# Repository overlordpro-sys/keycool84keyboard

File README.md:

# How I Made My Mechanical Keyboard ([Youtube Video](https://www.youtube.com/watch?v=BKlyYG0T2mQ))

About a year ago, I was looking into getting a new mechanical keyboard with linear switches. I had grown tired of the name brand keyboards like Corsair and Logitech who did not lubricate their switches. This made each keypress loud and unsatisfying. After doing some research, I decided to build my own instead of buying it. Most people who build custom keyboards buy a predesigned PCB. However, I wanted to design the PCB myself because I thought it would be fun. In the end, that proved true and I learned a lot about the inner workings of mechanical keyboards and PCB design. 

## Design

The switch layout I chose was the Keycool84 layout, featuring both arrow keys and a function row while still being relatively compact. After spending a day or two thinking about how to piece each component together, the design I went with featured a metal plate, 4 M4x10 bolts, two 3D printed supports for the bolts in the middle layer, and the PCB on the bottom. The bolts would also serve as a stand and create a slight incline. By using supports in between, I could avoid having to 3D print and piece together a large case that mechanical keyboards usually have. The Arduino would be placed to the side under one of the bolts. 

To get an accurate outline for the keyboard, I used the Keycool84 preset layout on keyboard-layout-editor.com.
In addition, I selected all of the keys and set each switch to use Cherry MX Kailh switch cutouts for my switch of choice, Kailh speed silvers, so I could use it to help with the plate cutout later on.

I transfered the raw data from the layout editor to a [plate and case builder website](http://builder.swillkb.com/) to generate a DXF file that I could actually use in KiCAD.

## Wiring

The most important part of this keyboard is naturally its wiring. Technically, each switch could be wired to two pins to detect switch input. This obviously is extremely inefficient and would use a lot of pins. The solution to this problem is wiring the switches in a gridlike manner. One issue with this, is that if multiple keys are pressed, some keypresses can be registered incorrectly due to current traveling backwards. This is solved by placing a diode with each switch to prevent this backwards flow and makes each keypress distinguishable from other keys by the Arduino. Each switch is wired approximately like so:

The last thing to consider was the location for each switch in the 6x14 grid. To get an idea of where each switch on the grid should be placed, I sketched it out in an app. 

## The PCB

The next step was designing the PCB for this keyboard. For simplicity and to ensure I had enough pins, I decided to use an Arduino Pro Micro for the controller. 
For the symbols and footprints for the switches and Arduino, I used two KiCad libraries:
https://github.com/ai03-2725/MX_Alps_Hybrid 
https://github.com/Biacco42/ProMicroKiCad 

For the necessary diodes, I downloaded the ECAD Model for the [1N4148W-7-F diode](https://www.mouser.co.uk/ProductDetail/Diodes-Incorporated/1N4148W-7-F?qs=LHX0FizJzg7Ae9ZM8LTAWw%3D%3D) at Mouser Electronics  and converted it into a KiCad library using the Mouser LibraryLoader. 

After including the libraries in my KiCad project file, I first wired the switches in a grid format in the schematics file. Then I assigned each row and column to a pin on the Arduino's symbol.

After I was finished with the schematic, I used KiCad's Pcbnew to design the PCB. Using the DXF file I generated before, I imported the file and moved each associated switch and diode footprint to each cutout on the DXF. I placed the Arduino's footprint to the left and drew a border around the entire PCB. To be able to secure my keyboard plate to the PCB, I also added four holes with a diameter slightly larger than the bolt diameter on each corner where I could use a nut and bolt. 

After placing all of the footprints, I routed the PCB using Freerouter. Overall, the board was simple and using an autorouter wouldn't cause any issues.

After adding some silkscreeneening out of curiosity, this was the finished result:

Using the built in 3D PCB viewer, took a look at the 3D model of what the PCB would look like. It was really neat seeing something I had designed myself.

After generating the neccessary Gerber files, I placed my order with JLCPCB and chose a white PCB. Here's what the PCBs looked like when they came:

## The Plate
The easiest way to maintain the same size and location for the screw holes was to make a copy of the old PCB file. After removing the switches, diodes, and Arduino footprints on the duplicate project, I ended up with a plain outline with screw holes. 

After exporting that to a DXF and removing any duplicate geometry in LibreCAD, it was ready to be cut.

After doing some research, I chose SendCutSend to cut my plate. In order for the switches to slot into the plate, the plate had to be a certain width, so the 0.060 inch (about 1.5mm) thick stainless steel material SendCutSend supplied was great. 

Unfortunately, I didn't take a very good picture before I soldered everything together, so this is the only picture I have of the plate by itself. 

## 3D Printing the middle

At first, I wanted to make a case that would encompass the entirety of the keyboard. However, the 3D printer I had at home would not be large enough to print it in one piece. Printing it in multiple pieces would require me to glue the pieces together and would make it less durable. I also didn't want to bother sending an order to a third party printing service and increasing my total build cost. At the very least, I wanted to make something that would fill some of the ugly gap between the plate and PCB. Filling in the gaps in the front and back of the keyboard would make it too large to print on my printer, so I could only make something for the right and left. In the end, I decided to make two rectangles with the cutouts for the bolts. 

In order to move it from KiCad to my modeling software of choice, Fusion 360, I plotted it into a DXF file and imported it with a 3.5mm thickness (approximate amount of space between the PCB and plate) using [DXF Import Utility.](https://apps.autodesk.com/FUSION/en/Detail/Index?id=3146198746757677787&appLang=en&os=Win64) 

After that, I exported each part into Cura with Fusion's built in exporter, merged the models into one project, and exported the G-code file for my 3D printer. 

## Software
To communicate the keystrokes, I used the Arduino libraries [Keypad](https://playground.arduino.cc/Code/Keypad/) and [Keyboard](https://www.arduino.cc/reference/en/language/functions/usb/keyboard/). The best thing about the Keypad library is that it supports N-key rollover to intepret multiple keypresses at the same time. For my keyboard, I edited Keypad's provided example. I added which keys I needed, edited the pins to use, and had it use Keyboard to send keystrokes instead of just printing them to console. 

```javascript
#include <Keypad.h>
#include <Keyboard.h>

const byte ROWS = 6;
const byte COLS = 14; 
char keys[ROWS][COLS] = {
  {KEY_ESC,KEY_F1,KEY_F2,KEY_F3,KEY_F4,KEY_F5,KEY_F6,KEY_F7,KEY_F8,KEY_F9,KEY_F10,KEY_F11,206,KEY_HOME},
  {'`','1','2','3','4','5','6','7','9','0','-',KEY_F12,KEY_INSERT,KEY_PAGE_UP},
  {KEY_TAB,'q','w','e','r','t','y','8','o','p','[','=',KEY_BACKSPACE,KEY_PAGE_DOWN},
  {KEY_CAPS_LOCK,'a','s','d','f','g','u','i','l',';',39,']',92,KEY_DELETE},
  {KEY_LEFT_SHIFT,'z','x','c','v','h','j','k','.','/',KEY_RIGHT_SHIFT,KEY_RETURN,KEY_UP_ARROW,' '},
  {KEY_LEFT_CTRL,KEY_LEFT_GUI,KEY_LEFT_ALT,32,'b','n','m',',',KEY_RIGHT_ALT,KEY_RIGHT_GUI,KEY_RIGHT_CTRL,KEY_LEFT_ARROW,KEY_DOWN_ARROW,KEY_RIGHT_ARROW}
};

byte rowPins[ROWS] = {18,19,20,21,22,23}; 
byte colPins[COLS] = {13,12,11,10,9,8,7,6,5,4,3,2,0,1}; 
Keypad kpd = Keypad( makeKeymap(keys), rowPins, colPins, ROWS, COLS );

void setup() {
    Keyboard.begin();
}

void loop() {
    if (kpd.getKeys())
    {
        for (int i=0; i<LIST_MAX; i++)   
        {
            if ( kpd.key[i].stateChanged )   
            {
                switch (kpd.key[i].kstate) { 
                    case PRESSED:
                    Keyboard.press(kpd.key[i].kchar);  
                break;
                    case HOLD:
                    Keyboard.press(kpd.key[i].kchar); 
                break;
                    case RELEASED:
                    Keyboard.release(kpd.key[i].kchar);  
                break;
                    case IDLE:
                break;
                }
            }
        }
    }
} 
```
## The Finished Product
After tediously placing and soldering each switch and surface mounted diode, it was almost complete. After fixing a small issue with my soldering using a spare wire and tightening the bolts, it was finished! If I do make a another keyboard in the future, I would definitely try to use something other than an Arduino that I could fully integrate into the PCB.

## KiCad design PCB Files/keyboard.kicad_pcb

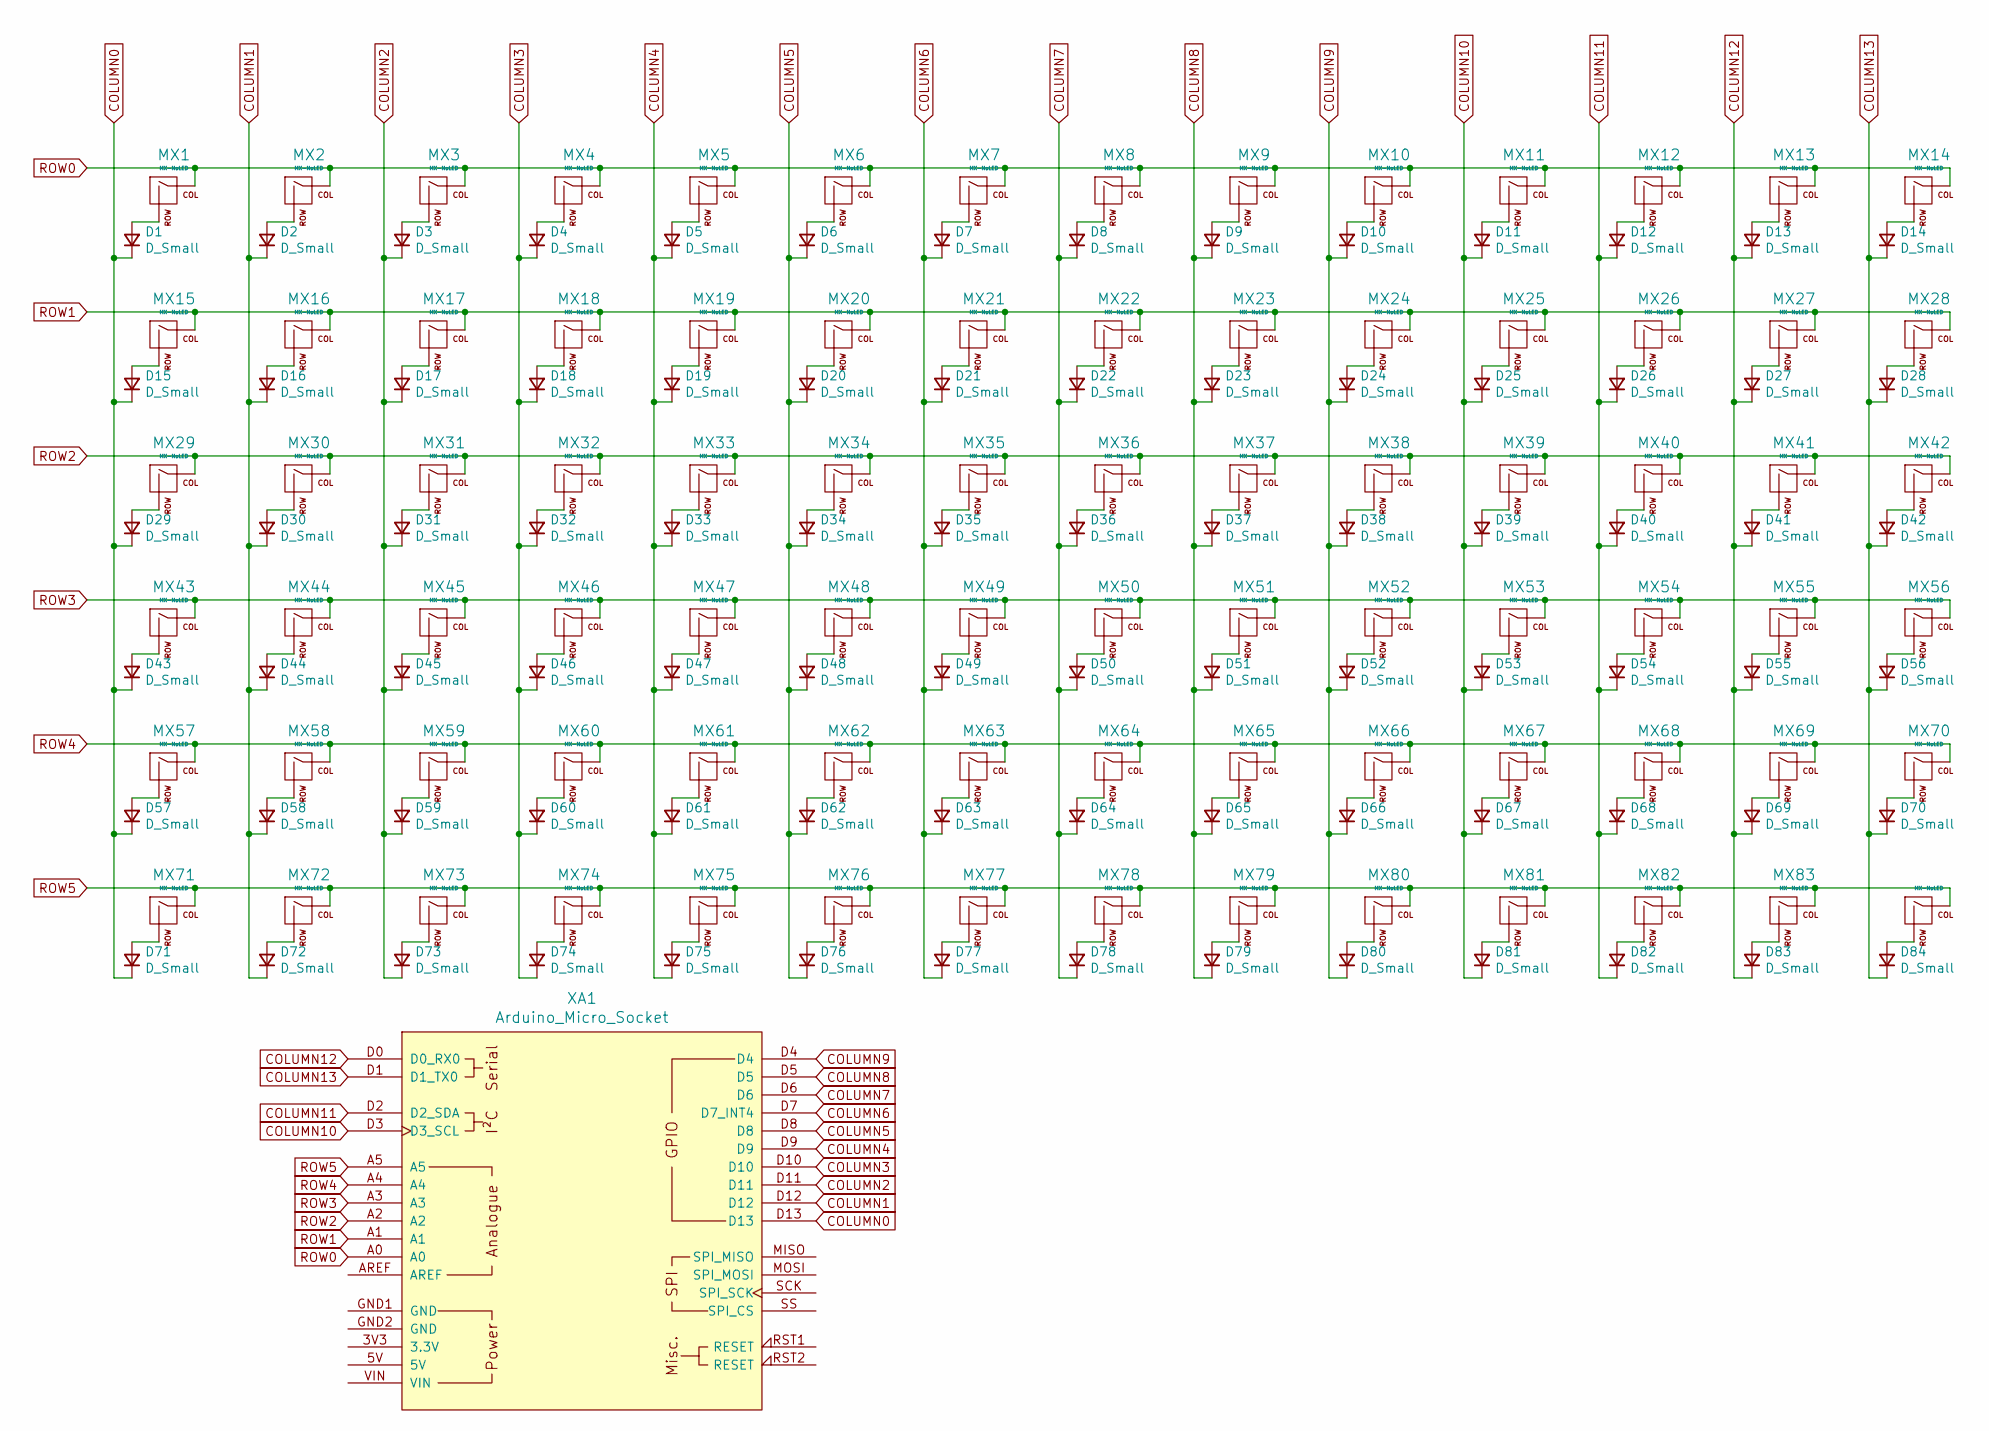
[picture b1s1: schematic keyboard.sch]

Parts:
D1, D2, D3, D4, D5, D6, D7, D8, D9, D10, D11, D12, D13, D14, D15, D16, D17, D18, D19, D20, D21, D22, D23, D24, D25, D26, D27, D28, D29, D30, D31, D32, D33, D34, D35, D36, D37, D38, D39, D40, D41, D42, D43, D44, D45, D46, D47, D48, D49, D50, D51, D52, D53, D54, D55, D56, D57, D58, D59, D60, D61, D62, D63, D64, D65, D66, D67, D68, D69, D70, D71, D72, D73, D74, D75, D76, D77, D78, D79, D80, D81, D82, D83, D84: D_Small; SOD3716X145N
MX1, MX2, MX3, MX4, MX5, MX6, MX7, MX8, MX9, MX10, MX11, MX12, MX13, MX14, MX15, MX16, MX17, MX18, MX19, MX20, MX21, MX22, MX23, MX24, MX25, MX26, MX27, MX28, MX30, MX31, MX32, MX33, MX34, MX35, MX36, MX37, MX38, MX39, MX40, MX42, MX44, MX45, MX46, MX47, MX48, MX49, MX50, MX51, MX52, MX53, MX54, MX56, MX58, MX59, MX60, MX61, MX62, MX63, MX64, MX65, MX66, MX69, MX70, MX75, MX76, MX77, MX78, MX79, MX80, MX81, MX82, MX83, MX84: MX-NoLED; MXOnly-1U-NoLED
MX29, MX55: MX-NoLED; MXOnly-1.5U-NoLED
MX41: MX-NoLED; MXOnly-2U-NoLED
MX43, MX67: MX-NoLED; MXOnly-1.75U-NoLED
MX57, MX68: MX-NoLED; MXOnly-2.25U-NoLED
MX71, MX72, MX73: MX-NoLED; MXOnly-1.25U-NoLED
MX74: MX-NoLED; MXOnly-6.25U-NoLED
XA1: Arduino_Micro_Socket

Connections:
COLUMN0: D1.1 (K), D15.1 (K), D29.1 (K), D43.1 (K), D57.1 (K), D71.1 (K), XA1.D13
COLUMN1: D2.1 (K), D16.1 (K), D30.1 (K), D44.1 (K), D58.1 (K), D72.1 (K), XA1.D12
COLUMN2: D3.1 (K), D17.1 (K), D31.1 (K), D45.1 (K), D59.1 (K), D73.1 (K), XA1.D11
COLUMN3: D4.1 (K), D18.1 (K), D32.1 (K), D46.1 (K), D60.1 (K), D74.1 (K), XA1.D10
COLUMN4: D5.1 (K), D19.1 (K), D33.1 (K), D47.1 (K), D61.1 (K), D75.1 (K), XA1.D9
COLUMN5: D6.1 (K), D20.1 (K), D34.1 (K), D48.1 (K), D62.1 (K), D76.1 (K), XA1.D8
COLUMN6: D7.1 (K), D21.1 (K), D35.1 (K), D49.1 (K), D63.1 (K), D77.1 (K), XA1.D7 (D7_INT4)
COLUMN7: D8.1 (K), D22.1 (K), D36.1 (K), D50.1 (K), D64.1 (K), D78.1 (K), XA1.D6
COLUMN8: D9.1 (K), D23.1 (K), D37.1 (K), D51.1 (K), D65.1 (K), D79.1 (K), XA1.D5
COLUMN9: D10.1 (K), D24.1 (K), D38.1 (K), D52.1 (K), D66.1 (K), D80.1 (K), XA1.D4
COLUMN10: D11.1 (K), D25.1 (K), D39.1 (K), D53.1 (K), D67.1 (K), D81.1 (K), XA1.D3 (D3_SCL)
COLUMN11: D12.1 (K), D26.1 (K), D40.1 (K), D54.1 (K), D68.1 (K), D82.1 (K), XA1.D2 (D2_SDA)
COLUMN12: D13.1 (K), D27.1 (K), D41.1 (K), D55.1 (K), D69.1 (K), D83.1 (K), XA1.D0 (D0_RX0)
COLUMN13: D14.1 (K), D28.1 (K), D42.1 (K), D56.1 (K), D70.1 (K), D84.1 (K), XA1.D1 (D1_TX0)
unnamed: D1.2 (A), MX1.2 (ROW)
unnamed: D2.2 (A), MX2.2 (ROW)
unnamed: D3.2 (A), MX3.2 (ROW)
unnamed: D4.2 (A), MX4.2 (ROW)
unnamed: D5.2 (A), MX5.2 (ROW)
unnamed: D6.2 (A), MX6.2 (ROW)
unnamed: D7.2 (A), MX7.2 (ROW)
unnamed: D8.2 (A), MX8.2 (ROW)
unnamed: D9.2 (A), MX9.2 (ROW)
unnamed: D10.2 (A), MX10.2 (ROW)
unnamed: D11.2 (A), MX11.2 (ROW)
unnamed: D12.2 (A), MX12.2 (ROW)
unnamed: D13.2 (A), MX13.2 (ROW)
unnamed: D14.2 (A), MX14.2 (ROW)
unnamed: D15.2 (A), MX15.2 (ROW)
unnamed: D16.2 (A), MX16.2 (ROW)
unnamed: D17.2 (A), MX17.2 (ROW)
unnamed: D18.2 (A), MX18.2 (ROW)
unnamed: D19.2 (A), MX19.2 (ROW)
unnamed: D20.2 (A), MX20.2 (ROW)
unnamed: D21.2 (A), MX21.2 (ROW)
unnamed: D22.2 (A), MX22.2 (ROW)
unnamed: D23.2 (A), MX23.2 (ROW)
unnamed: D24.2 (A), MX24.2 (ROW)
unnamed: D25.2 (A), MX25.2 (ROW)
unnamed: D26.2 (A), MX26.2 (ROW)
unnamed: D27.2 (A), MX27.2 (ROW)
unnamed: D28.2 (A), MX28.2 (ROW)
unnamed: D29.2 (A), MX29.2 (ROW)
unnamed: D30.2 (A), MX30.2 (ROW)
unnamed: D31.2 (A), MX31.2 (ROW)
unnamed: D32.2 (A), MX32.2 (ROW)
unnamed: D33.2 (A), MX33.2 (ROW)
unnamed: D34.2 (A), MX34.2 (ROW)
unnamed: D35.2 (A), MX35.2 (ROW)
unnamed: D36.2 (A), MX36.2 (ROW)
unnamed: D37.2 (A), MX37.2 (ROW)
unnamed: D38.2 (A), MX38.2 (ROW)
unnamed: D39.2 (A), MX39.2 (ROW)
unnamed: D40.2 (A), MX40.2 (ROW)
unnamed: D41.2 (A), MX41.2 (ROW)
unnamed: D42.2 (A), MX42.2 (ROW)
unnamed: D43.2 (A), MX43.2 (ROW)
unnamed: D44.2 (A), MX44.2 (ROW)
unnamed: D45.2 (A), MX45.2 (ROW)
unnamed: D46.2 (A), MX46.2 (ROW)
unnamed: D47.2 (A), MX47.2 (ROW)
unnamed: D48.2 (A), MX48.2 (ROW)
unnamed: D49.2 (A), MX49.2 (ROW)
unnamed: D50.2 (A), MX50.2 (ROW)
unnamed: D51.2 (A), MX51.2 (ROW)
unnamed: D52.2 (A), MX52.2 (ROW)
unnamed: D53.2 (A), MX53.2 (ROW)
unnamed: D54.2 (A), MX54.2 (ROW)
unnamed: D55.2 (A), MX55.2 (ROW)
unnamed: D56.2 (A), MX56.2 (ROW)
unnamed: D57.2 (A), MX57.2 (ROW)
unnamed: D58.2 (A), MX58.2 (ROW)
unnamed: D59.2 (A), MX59.2 (ROW)
unnamed: D60.2 (A), MX60.2 (ROW)
unnamed: D61.2 (A), MX61.2 (ROW)
unnamed: D62.2 (A), MX62.2 (ROW)
unnamed: D63.2 (A), MX63.2 (ROW)
unnamed: D64.2 (A), MX64.2 (ROW)
unnamed: D65.2 (A), MX65.2 (ROW)
unnamed: D66.2 (A), MX66.2 (ROW)
unnamed: D67.2 (A), MX67.2 (ROW)
unnamed: D68.2 (A), MX68.2 (ROW)
unnamed: D69.2 (A), MX69.2 (ROW)
unnamed: D70.2 (A), MX70.2 (ROW)
unnamed: D71.2 (A), MX71.2 (ROW)
unnamed: D72.2 (A), MX72.2 (ROW)
unnamed: D73.2 (A), MX73.2 (ROW)
unnamed: D74.2 (A), MX74.2 (ROW)
unnamed: D75.2 (A), MX75.2 (ROW)
unnamed: D76.2 (A), MX76.2 (ROW)
unnamed: D77.2 (A), MX77.2 (ROW)
unnamed: D78.2 (A), MX78.2 (ROW)
unnamed: D79.2 (A), MX79.2 (ROW)
unnamed: D80.2 (A), MX80.2 (ROW)
unnamed: D81.2 (A), MX81.2 (ROW)
unnamed: D82.2 (A), MX82.2 (ROW)
unnamed: D83.2 (A), MX83.2 (ROW)
unnamed: D84.2 (A), MX84.2 (ROW)
ROW0: MX1.1 (COL), MX2.1 (COL), MX3.1 (COL), MX4.1 (COL), MX5.1 (COL), MX6.1 (COL), MX7.1 (COL), MX8.1 (COL), MX9.1 (COL), MX10.1 (COL), MX11.1 (COL), MX12.1 (COL), MX13.1 (COL), MX14.1 (COL), XA1.A0
ROW1: MX15.1 (COL), MX16.1 (COL), MX17.1 (COL), MX18.1 (COL), MX19.1 (COL), MX20.1 (COL), MX21.1 (COL), MX22.1 (COL), MX23.1 (COL), MX24.1 (COL), MX25.1 (COL), MX26.1 (COL), MX27.1 (COL), MX28.1 (COL), XA1.A1
ROW2: MX29.1 (COL), MX30.1 (COL), MX31.1 (COL), MX32.1 (COL), MX33.1 (COL), MX34.1 (COL), MX35.1 (COL), MX36.1 (COL), MX37.1 (COL), MX38.1 (COL), MX39.1 (COL), MX40.1 (COL), MX41.1 (COL), MX42.1 (COL), XA1.A2
ROW3: MX43.1 (COL), MX44.1 (COL), MX45.1 (COL), MX46.1 (COL), MX47.1 (COL), MX48.1 (COL), MX49.1 (COL), MX50.1 (COL), MX51.1 (COL), MX52.1 (COL), MX53.1 (COL), MX54.1 (COL), MX55.1 (COL), MX56.1 (COL), XA1.A3
ROW4: MX57.1 (COL), MX58.1 (COL), MX59.1 (COL), MX60.1 (COL), MX61.1 (COL), MX62.1 (COL), MX63.1 (COL), MX64.1 (COL), MX65.1 (COL), MX66.1 (COL), MX67.1 (COL), MX68.1 (COL), MX69.1 (COL), MX70.1 (COL), XA1.A4
ROW5: MX71.1 (COL), MX72.1 (COL), MX73.1 (COL), MX74.1 (COL), MX75.1 (COL), MX76.1 (COL), MX77.1 (COL), MX78.1 (COL), MX79.1 (COL), MX80.1 (COL), MX81.1 (COL), MX82.1 (COL), MX83.1 (COL), MX84.1 (COL), XA1.A5

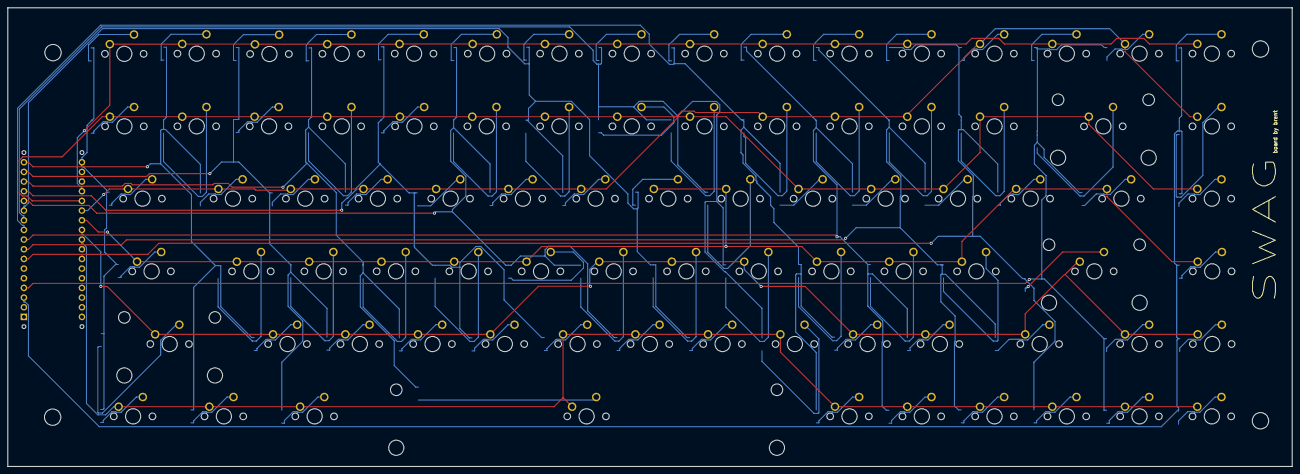
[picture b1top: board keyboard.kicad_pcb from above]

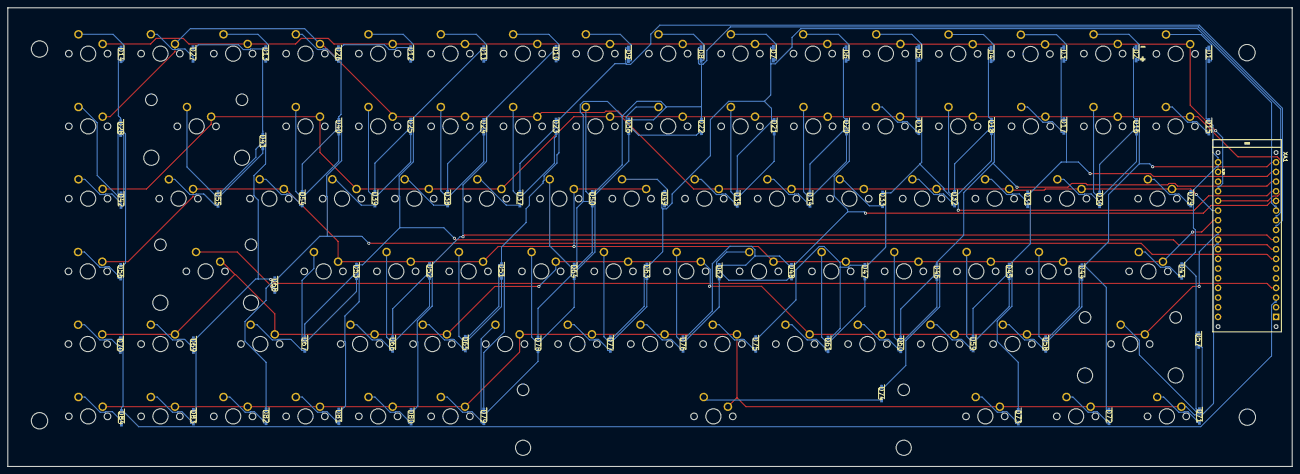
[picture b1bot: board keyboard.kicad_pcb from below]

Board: 2 copper layers, 337.4 x 120.5 mm, 173 parts (85 on the bottom side), 104 nets.

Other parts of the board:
bolthole1, bolthole2, bolthole3, bolthole4: MountingHole_4.3mm_M4

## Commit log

2022-03-06 added how keyboard was made; unfinished
2022-07-22 Create temp
2022-07-22 new directory
2022-07-22 Rename plate.dxf to keyboardfiles/plate.dxf
2022-07-22 Uploaded gerber files
2022-07-22 Uploaded gerber file
2022-07-22 Added files for 3D printed middle supports
    Added CURA project 3mf files
2022-08-03 Renamed Folder
2022-08-03 Added PCB Files for Main Board
2022-08-16 Added arduino sketch because I forgot
    oops
2022-08-26 Fixed typo
2022-08-29 Added MX Switches Library Folder
    Forgot
